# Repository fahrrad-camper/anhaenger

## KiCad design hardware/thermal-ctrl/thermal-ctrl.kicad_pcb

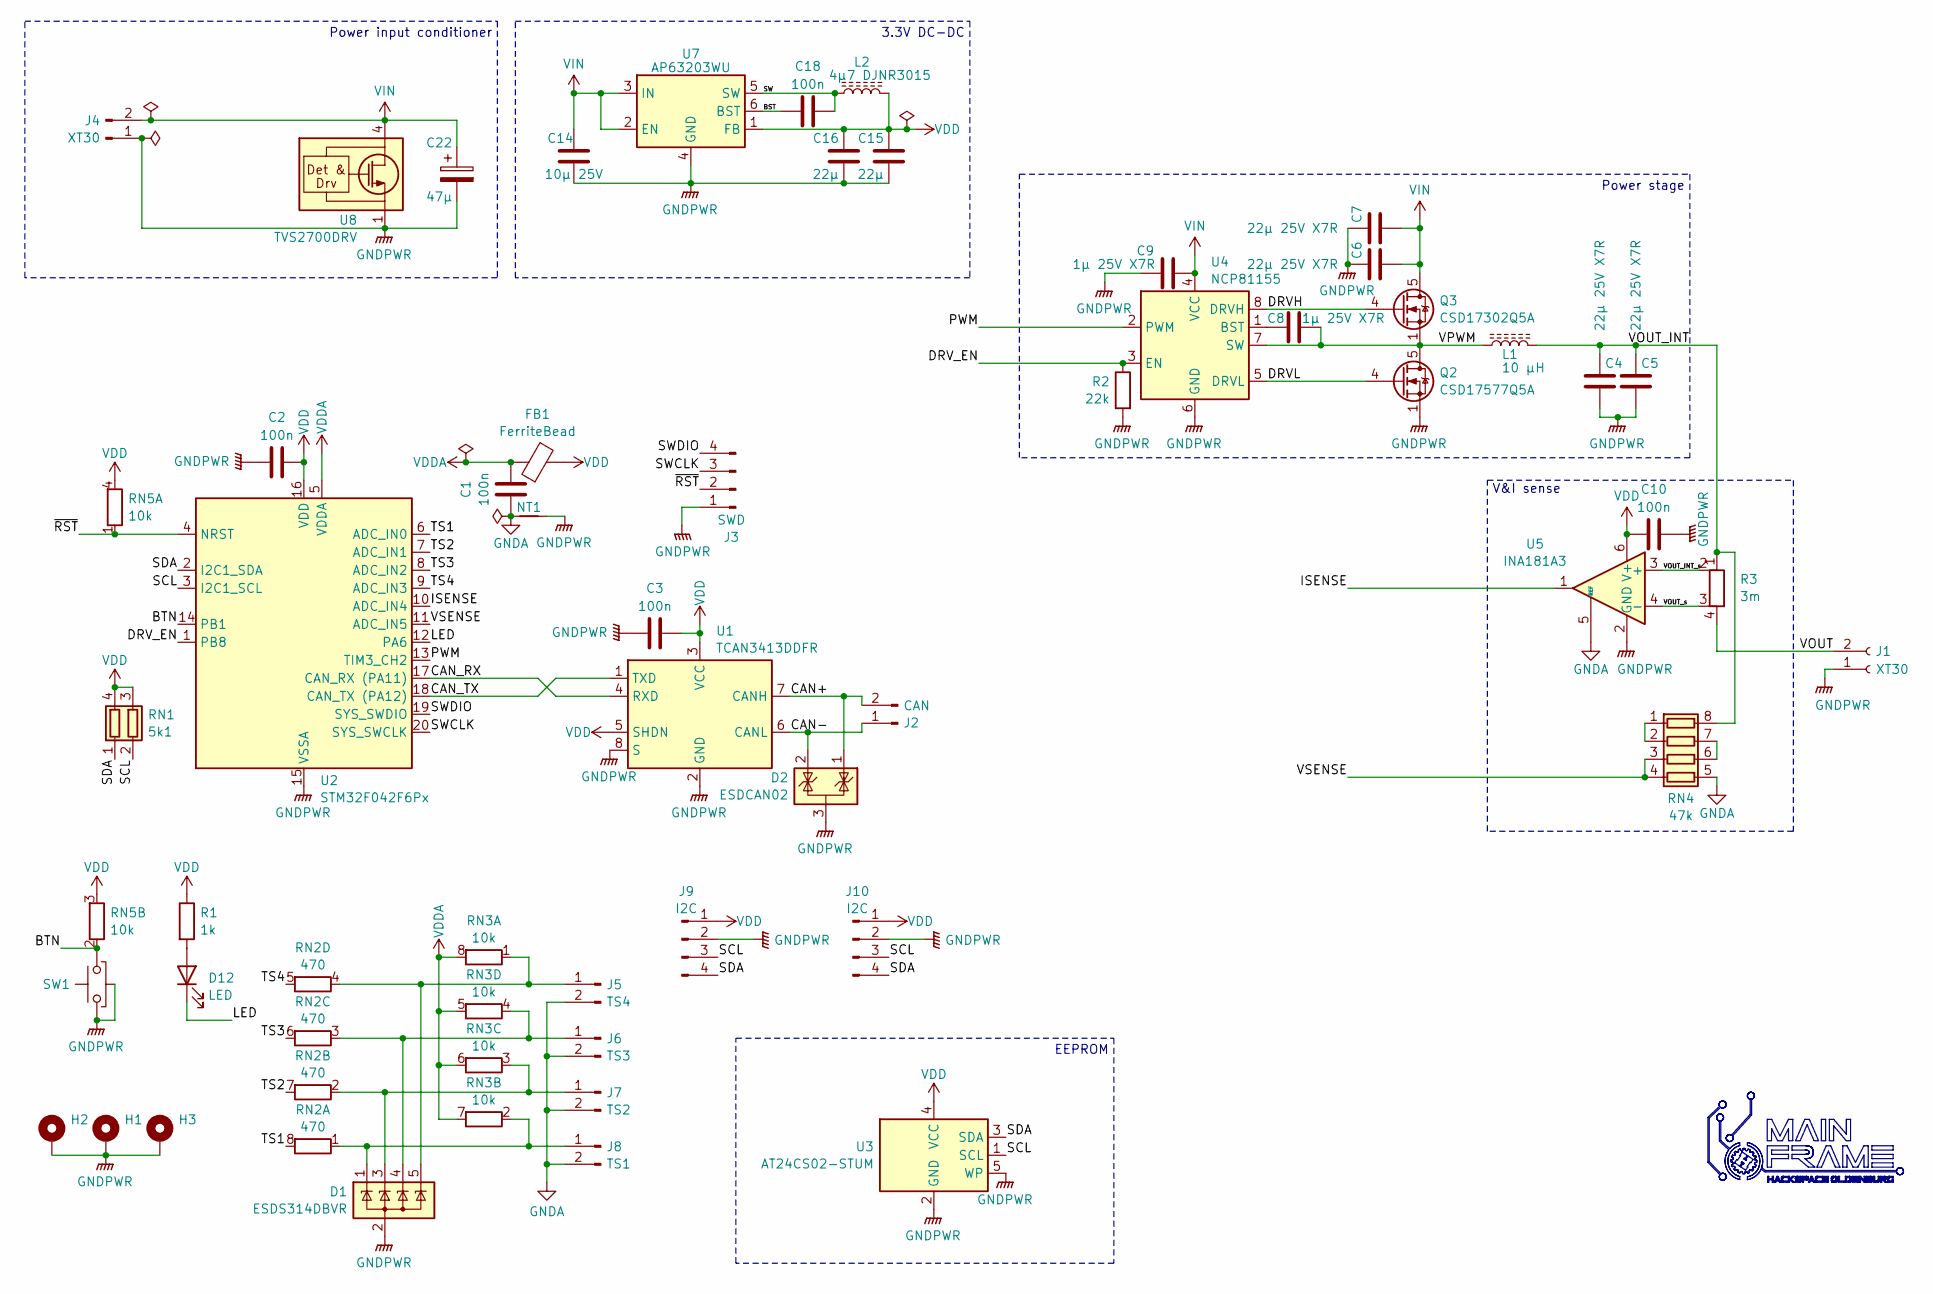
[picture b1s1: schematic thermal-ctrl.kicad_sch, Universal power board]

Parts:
C1, C2, C3, C10, C18: 100n; C_0603_1608Metric
C4, C5, C6, C7: 22µ 25V X7R; C_1210_3225Metric
C8, C9: 1µ 25V X7R; C_0603_1608Metric
C14: 10µ 25V; C_0805_2012Metric
C15, C16: 22µ; C_0805_2012Metric
C22: 47µ; CP_Elec_6.3x5.4
D1: ESDS314DBVR; SOT-23-5
D2: ESDCAN02; SOT-323_SC-70
D12: LED; LED_Kingbright_APDA3020VBCD
FB1: FerriteBead; L_0603_1608Metric
H1, H2, H3: M3; MountingHole_3.2mm_M3_ISO7380_Pad_TopBottom
J1: XT30; AMASS_XT30PW-F_1x02_P2.50mm_Horizontal
J2: CAN; PhoenixContact_MC_1,5_2-G-3.5_1x02_P3.50mm_Horizontal
J3: SWD; PinHeader_1x04_P1.27mm_Vertical
J4: XT30; AMASS_XT30PW-M_1x02_P2.50mm_Horizontal
J5: TS4; JST_XH_B2B-XH-A_1x02_P2.50mm_Vertical
J6: TS3; JST_XH_B2B-XH-A_1x02_P2.50mm_Vertical
J7: TS2; JST_XH_B2B-XH-A_1x02_P2.50mm_Vertical
J8: TS1; JST_XH_B2B-XH-A_1x02_P2.50mm_Vertical
J9, J10: I2C; JST_XH_B4B-XH-A_1x04_P2.50mm_Vertical
L1: 10 µH; L_Bourns_SRP1245A
L2: 4µ7 DJNR3015; L_Neosid_SMS-ME3015
NT1: NetTie_2; NetTie-2_SMD_Pad0.5mm
Q2: CSD17577Q5A; LFPAK56
Q3: CSD17302Q5A; LFPAK56
R1: 1k; R_0603_1608Metric
R2: 22k; R_0603_1608Metric
R3: 3m; R_Shunt_2512_6332Metric_KelvinConnection
RN1: 5k1; R_Array_Convex_2x0603
RN2: 470; R_Array_Convex_4x0603
RN3: 10k; R_Array_Convex_4x0603
RN4: 47k; R_Array_Convex_4x0603
RN5: 10k; R_Array_Convex_2x0603
SW1: SW_Tactile_SPST_Angled_PTS645Vx31-2LFS
U1: TCAN3413DDFR; TSOT-23-8
U2: STM32F042F6Px; TSSOP-20_4.4x6.5mm_P0.65mm
U3: AT24CS02-STUM; SOT-353_SC-70-5
U4: NCP81155; DFN-8-1EP_3x3mm_P0.5mm_EP1.55x1.85mm
U5: INA181A3; SOT-23-6
U7: AP63203WU; TSOT-23-6
U8: TVS2700DRV; WSON-6-1EP_2x2mm_P0.65mm_EP1x1.6mm

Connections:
/BST: C18.1, U7.6 (BST)
/BTN: RN5.2 (R2.1), SW1.2, U2.14 (PB1)
/CAN+: D2.1 (K), J2.2, U1.7 (CANH)
/CAN-: D2.2 (K), J2.1, U1.6 (CANL)
/CAN_RX: U1.4 (RXD), U2.17 (CAN_RX (PA11))
/CAN_TX: U1.1 (TXD), U2.18 (CAN_TX (PA12))
/DRVH: Q3.4 (G), U4.8 (DRVH)
/DRVL: Q2.4 (G), U4.5 (DRVL)
/DRV_EN: R2.1, U2.1 (PB8), U4.3 (EN)
/ISENSE: U2.10 (ADC_IN4), U5.1
/LED: D12.1 (K), U2.12 (PA6)
/PWM: U2.13 (TIM3_CH2), U4.2 (PWM)
/SCL: J9.3, J10.3, RN1.2 (R2.1), U2.3 (I2C1_SCL), U3.1 (SCL)
/SDA: J9.4, J10.4, RN1.1 (R1.1), U2.2 (I2C1_SDA), U3.3 (SDA)
/SW: C18.2, L2.1, U7.5 (SW)
/SWCLK: J3.3, U2.20 (SYS_SWCLK)
/SWDIO: J3.4, U2.19 (SYS_SWDIO)
/TS1: RN2.8 (R1.2), U2.6 (ADC_IN0)
/TS2: RN2.7 (R2.2), U2.7 (ADC_IN1)
/TS3: RN2.6 (R3.2), U2.8 (ADC_IN2)
/TS4: RN2.5 (R4.2), U2.9 (ADC_IN3)
/VOUT: J1.2, R3.4
/VOUT_INT: C4.1, C5.1, L1.2, R3.1, RN4.8 (R1.2)
/VOUT_INT_s: R3.2, U5.3 (+)
/VOUT_s: R3.3, U5.4 (-)
/VPWM: C8.2, L1.1, Q2.5 (D), Q3.1 (S), Q3.2 (S), Q3.3 (S), U4.7 (SW)
/VSENSE: RN4.3 (R3.1), RN4.4 (R4.1), U2.11 (ADC_IN5)
/~RST: J3.2, RN5.1 (R1.1), U2.4 (NRST)
GNDA: C1.1, J5.2, J6.2, J7.2, J8.2, NT1.1, RN4.5 (R4.2), U5.5 (REF)
GNDPWR: C2.1, C3.1, C4.2, C5.2, C6.1, C7.1, C9.1, C10.1, C14.1, C15.1, C16.1, C22.2, D1.2 (A), D2.3 (A), H1.1, H2.1, H3.1, J1.1, J3.1, J4.1, J9.2, J10.2, NT1.2, Q2.1 (S), Q2.2 (S), Q2.3 (S), R2.2, SW1.1, SW1.MP, U1.2 (GND), U1.8 (S), U2.15 (VSSA), U3.2 (GND), U3.5 (WP), U4.6 (GND), U4.9 (FLAG), U5.2 (GND), U7.4 (GND), U8.1 (GND), U8.2 (GND), U8.3 (GND), U8.7 (GND)
unnamed: D12.2 (A), R1.2
unnamed: D1.5 (K), J5.1, RN2.4 (R4.1), RN3.1 (R1.1)
unnamed: D1.4 (K), J6.1, RN2.3 (R3.1), RN3.4 (R4.1)
unnamed: D1.3 (K), J7.1, RN2.2 (R2.1), RN3.3 (R3.1)
unnamed: D1.1 (K), J8.1, RN2.1 (R1.1), RN3.2 (R2.1)
unnamed: RN4.1 (R1.1), RN4.2 (R2.1)
unnamed: RN4.6 (R3.2), RN4.7 (R2.2)
unnamed: C8.1, U4.1 (BST)
VDD: C2.2, C3.2, C10.2, C15.2, C16.2, FB1.2, J9.1, J10.1, L2.2, R1.1, RN1.3 (R2.2), RN1.4 (R1.2), RN5.3 (R2.2), RN5.4 (R1.2), U1.3 (VCC), U1.5 (SHDN), U2.16 (VDD), U3.4 (VCC), U5.6 (V+), U7.1 (FB)
VDDA: C1.2, FB1.1, RN3.5 (R4.2), RN3.6 (R3.2), RN3.7 (R2.2), RN3.8 (R1.2), U2.5 (VDDA)
VIN: C6.2, C7.2, C9.2, C14.2, C22.1, J4.2, Q3.5 (D), U4.4 (VCC), U7.2 (EN), U7.3 (IN), U8.4 (IN), U8.5 (IN), U8.6 (IN)

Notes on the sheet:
EEPROM
Power stage
Power input conditioner
V&I sense
3.3V DC-DC

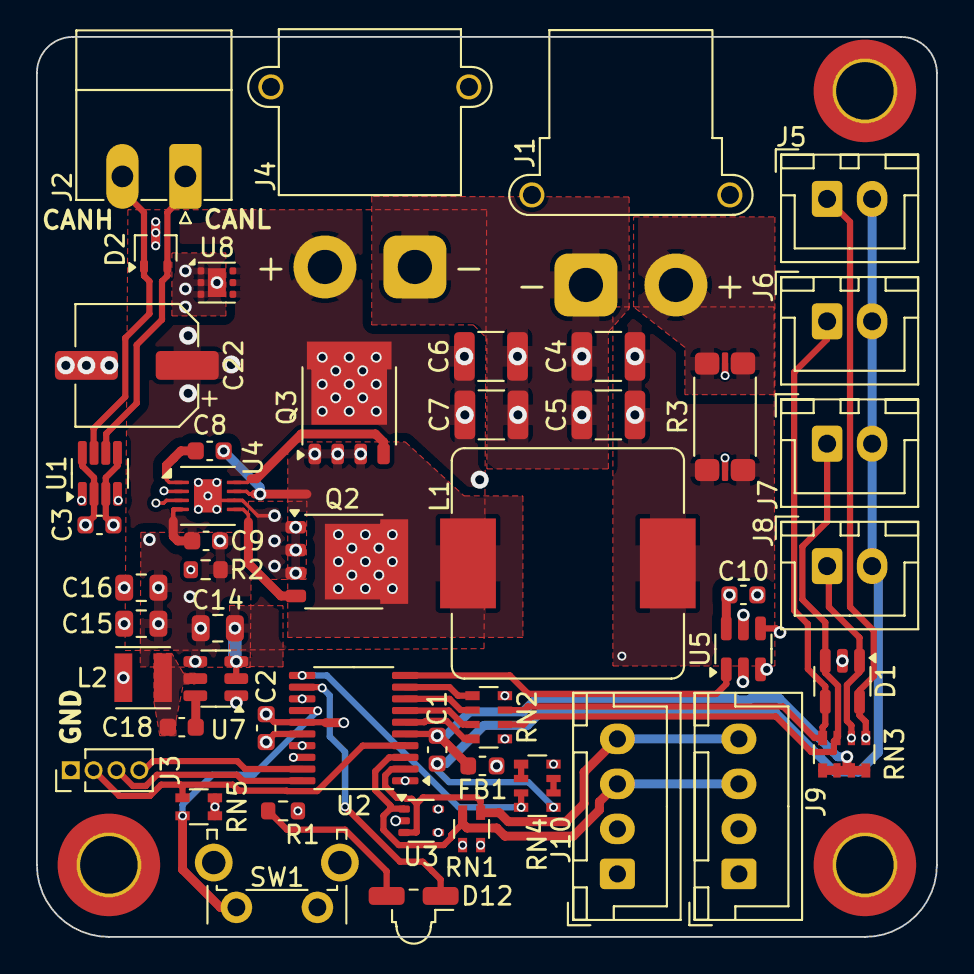
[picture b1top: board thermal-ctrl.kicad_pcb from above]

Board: 6 copper layers, 50.0 x 50.0 mm, 53 parts (0 on the bottom side), 41 nets.

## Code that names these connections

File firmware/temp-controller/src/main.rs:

#![feature(impl_trait_in_assoc_type)]
#![no_std]
#![no_main]

mod adc;
mod can;
mod ntc;
mod pwm;
mod tbh;
mod temperature;
mod traits;

mod power_regulator;

use {defmt_rtt as _, panic_probe as _};

use crate::{
    adc::AdcReader, can::process as can_process, pwm::Pwm,
    temperature::process as temperature_process,
    tbh::Tbh,
    power_regulator::PowerRegulator,
    traits::{AsInput, Regulator},
};

use core::{
    cell::RefCell,
    sync::atomic::{AtomicBool, AtomicU8, Ordering},
};
use defmt::{info, unwrap, Debug2Format};
use embassy_embedded_hal::shared_bus::asynch::i2c::I2cDevice;
use embassy_executor::{main, task, Spawner};
use embassy_futures::{yield_now, select::select};
use embassy_stm32::{
    adc::{self as stm32_adc, Adc, AdcChannel},
    bind_interrupts,
    can::{self as stm32_can, Can},
    dma,
    exti::{self, ExtiInput},
    gpio::{Flex, Input, Level, Output, OutputOpenDrain, OutputType, Pull, Speed},
    i2c::{self, Config as I2cConfig, I2c},
    mode::Async,
    pac, peripherals,
    time::{khz, mhz},
    timer::{
        low_level::{CountingMode, OutputPolarity},
        simple_pwm::{PwmPin, SimplePwm},
    },
    wdg::IndependentWatchdog,
    Config as DeviceConfig,
};
use embassy_sync::{blocking_mutex::raw::NoopRawMutex, mutex::Mutex};
use embassy_time::{Instant, Timer};
use static_cell::StaticCell;

bind_interrupts!(struct Irqs {
    I2C1 => i2c::EventInterruptHandler<peripherals::I2C1>, i2c::ErrorInterruptHandler<peripherals::I2C1>;
    ADC1 => stm32_adc::InterruptHandler<peripherals::ADC1>;
    CEC_CAN => stm32_can::Rx0InterruptHandler<peripherals::CAN>, stm32_can::Rx1InterruptHandler<peripherals::CAN>,
               stm32_can::TxInterruptHandler<peripherals::CAN>, stm32_can::SceInterruptHandler<peripherals::CAN>;
    DMA1_CHANNEL2_3 => dma::InterruptHandler<peripherals::DMA1_CH2>, dma::InterruptHandler<peripherals::DMA1_CH3>;
});

static PWM_DUTY: AtomicU8 = AtomicU8::new(0);

#[main]
async fn main(spawner: Spawner) {
    // HSI oscillator 12 MHz, 64 MHz system frequency
    let mut config = DeviceConfig::default();
    {
        use embassy_stm32::rcc::*;
        config.rcc.hsi = true;
        config.rcc.hse = None;
        config.rcc.pll = Some(Pll {
            src: PllSource::HSI,
            prediv: PllPreDiv::DIV1,
            mul: PllMul::MUL6,
        });
        config.rcc.sys = Sysclk::PLL1_P;
        config.rcc.ahb_pre = AHBPrescaler::DIV1;
        config.rcc.apb1_pre = APBPrescaler::DIV1;
        config.enable_debug_during_sleep = true;
    }
    let dev = embassy_stm32::init(config);

    // Reconfigure pins for CAN bus
    pac::SYSCFG.cfgr1().modify(|w| w.set_pa11_pa12_rmp(true));

    let sda = dev.PF0;
    let scl = dev.PF1;
    let i2c = I2c::new(dev.I2C1, scl, sda, dev.DMA1_CH2, dev.DMA1_CH3, Irqs, {
        let mut cfg = I2cConfig::default();
        cfg.frequency = khz(400);
        cfg
    });

    let adc = Adc::new(dev.ADC1, Irqs);
    let adc = AdcReader {
        adc,
        ts: [
            dev.PA0.degrade_adc(),
            dev.PA1.degrade_adc(),
            dev.PA2.degrade_adc(),
            dev.PA3.degrade_adc(),
        ],
        vsense: dev.PA5.degrade_adc(),
        isense: dev.PA4.degrade_adc(),
    };
    let mut adc = adc.init();

    //    unwrap!(spawner.spawn(temperature_process(i2c)));

    let can = Can::new(dev.CAN, dev.PA11, dev.PA12, Irqs);
    //spawner.spawn(can_process(can).unwrap());

    let pwm = PwmPin::new(dev.PA7, OutputType::PushPull);
    let pwm = SimplePwm::new(
        dev.TIM3,
        None,
        Some(pwm),
        None,
        None,
        khz(400),
        CountingMode::EdgeAlignedUp,
    );
    let mut pwm = pwm.split().ch2;
    pwm.set_polarity(OutputPolarity::ActiveHigh);
    pwm.set_duty_cycle_fully_off();
    pwm.enable();

    let drv_en = Output::new(dev.PB8, Level::Low, Speed::Low);

    let pwm = Pwm::new(pwm, drv_en, 0.1);

    let mut led = OutputOpenDrain::new(dev.PA6, Level::High, Speed::Low);

    let power_regulator = PowerRegulator::new(pwm);
    let mut temperature_regulator = Tbh::new(0.0005, power_regulator, 10.0);

    loop {
        led.toggle();
        let t = Instant::now();
        let reading = adc.read().await;
        let temperature = reading.ts[0] as f32 / 1_000.0;
        info!("T = {}", temperature);
        let power = reading.output_current_ma as f32 * reading.output_voltage_mv as f32 / 1_000_000.0;
        let input = Inputs {
            power,
            temperature,
        };
        temperature_regulator.regulate(t, &input, 45.0);
        Timer::after_millis(200).await;
    }
}

struct Inputs {
    power: f32,
    temperature: f32,
}

impl<T> AsInput<PowerRegulator<T>> for Inputs {
    type Value = f32;
    fn as_input(&self) -> Self::Value {
        self.power
    }
}

impl<T> AsInput<Tbh<T>> for Inputs {
    type Value = f32;
    fn as_input(&self) -> Self::Value {
        self.temperature
    }
}

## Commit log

2026-05-06 Implement NTC conversion
2026-05-06 Update Embassy version
2026-06-13 Update everything

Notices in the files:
hardware/thermal-ctrl/thermal-ctrl.kicad_pcb:
CC-BY-NC-SA Alexey Galakhov
